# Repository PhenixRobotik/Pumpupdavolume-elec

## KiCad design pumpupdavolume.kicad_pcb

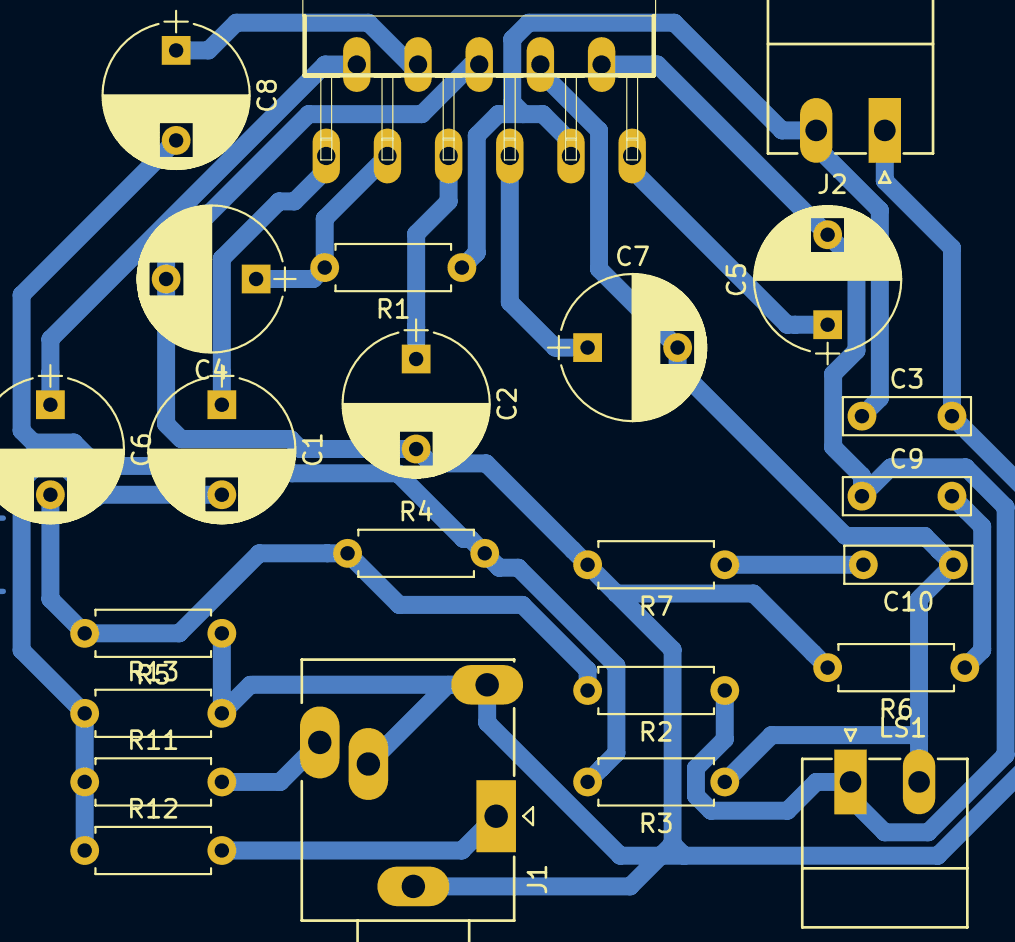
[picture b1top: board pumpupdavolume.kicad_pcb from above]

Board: 2 copper layers, 24 parts (0 on the bottom side), 18 nets.

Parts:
C1, C2: 2.2 uF; CP_Radial_D8.0mm_P5.00mm
C3, C9, C10: 0.1 uF; C_Rect_L7.0mm_W2.0mm_P5.00mm
C4: 10 uF; CP_Radial_D8.0mm_P5.00mm
C5, C7: 100uF; CP_Radial_D8.0mm_P5.00mm
C6, C8: 220 uF; CP_Radial_D8.0mm_P5.00mm
J1: AudioJack3_Switch; Jack_3.5mm_Ledino_KB3SPRS_Horizontal
J2: Conn_01x02_Male; PhoenixContact_MC-G_02x3.81mm_Angled
LS1: Speaker; PhoenixContact_MC-G_02x3.81mm_Angled
R1: 120k; R_Axial_DIN0207_L6.3mm_D2.5mm_P7.62mm_Horizontal
R2: 1k; R_Axial_DIN0207_L6.3mm_D2.5mm_P7.62mm_Horizontal
R3: 2k; R_Axial_DIN0207_L6.3mm_D2.5mm_P7.62mm_Horizontal
R4, R5: 12; R_Axial_DIN0207_L6.3mm_D2.5mm_P7.62mm_Horizontal
R6, R7: 1; R_Axial_DIN0207_L6.3mm_D2.5mm_P7.62mm_Horizontal
R11, R12, R13: R; R_Axial_DIN0207_L6.3mm_D2.5mm_P7.62mm_Horizontal
U1: TDA2005; st-microelectronics-MULTIWATT-11

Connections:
GND: C2.2, C3.2, C4.2, J1.RN, J1.S, J1.TN, J2.1, R5.1, R6.2, R7.2, R13.2, U1.6
unnamed: C1.1, U1.1
unnamed: C1.2, R11.1, R12.1, R13.1
unnamed: C2.1, U1.5
unnamed: C4.1, R1.2, U1.3
unnamed: C5.1, U1.11
unnamed: C5.2, C9.1, LS1.1, R2.1, U1.10
unnamed: C6.1, U1.2
unnamed: C6.2, R2.2, R4.1, R5.2
unnamed: C7.1, U1.7
unnamed: C8.1, U1.4
unnamed: C8.2, R3.2, R4.2
unnamed: C9.2, R6.1
unnamed: C7.2, C10.1, LS1.2, R3.1, U1.8
unnamed: C10.2, R7.1
unnamed: J1.R, R11.2
unnamed: J1.T, R12.2
VS: C3.1, J2.2, R1.1, U1.9
